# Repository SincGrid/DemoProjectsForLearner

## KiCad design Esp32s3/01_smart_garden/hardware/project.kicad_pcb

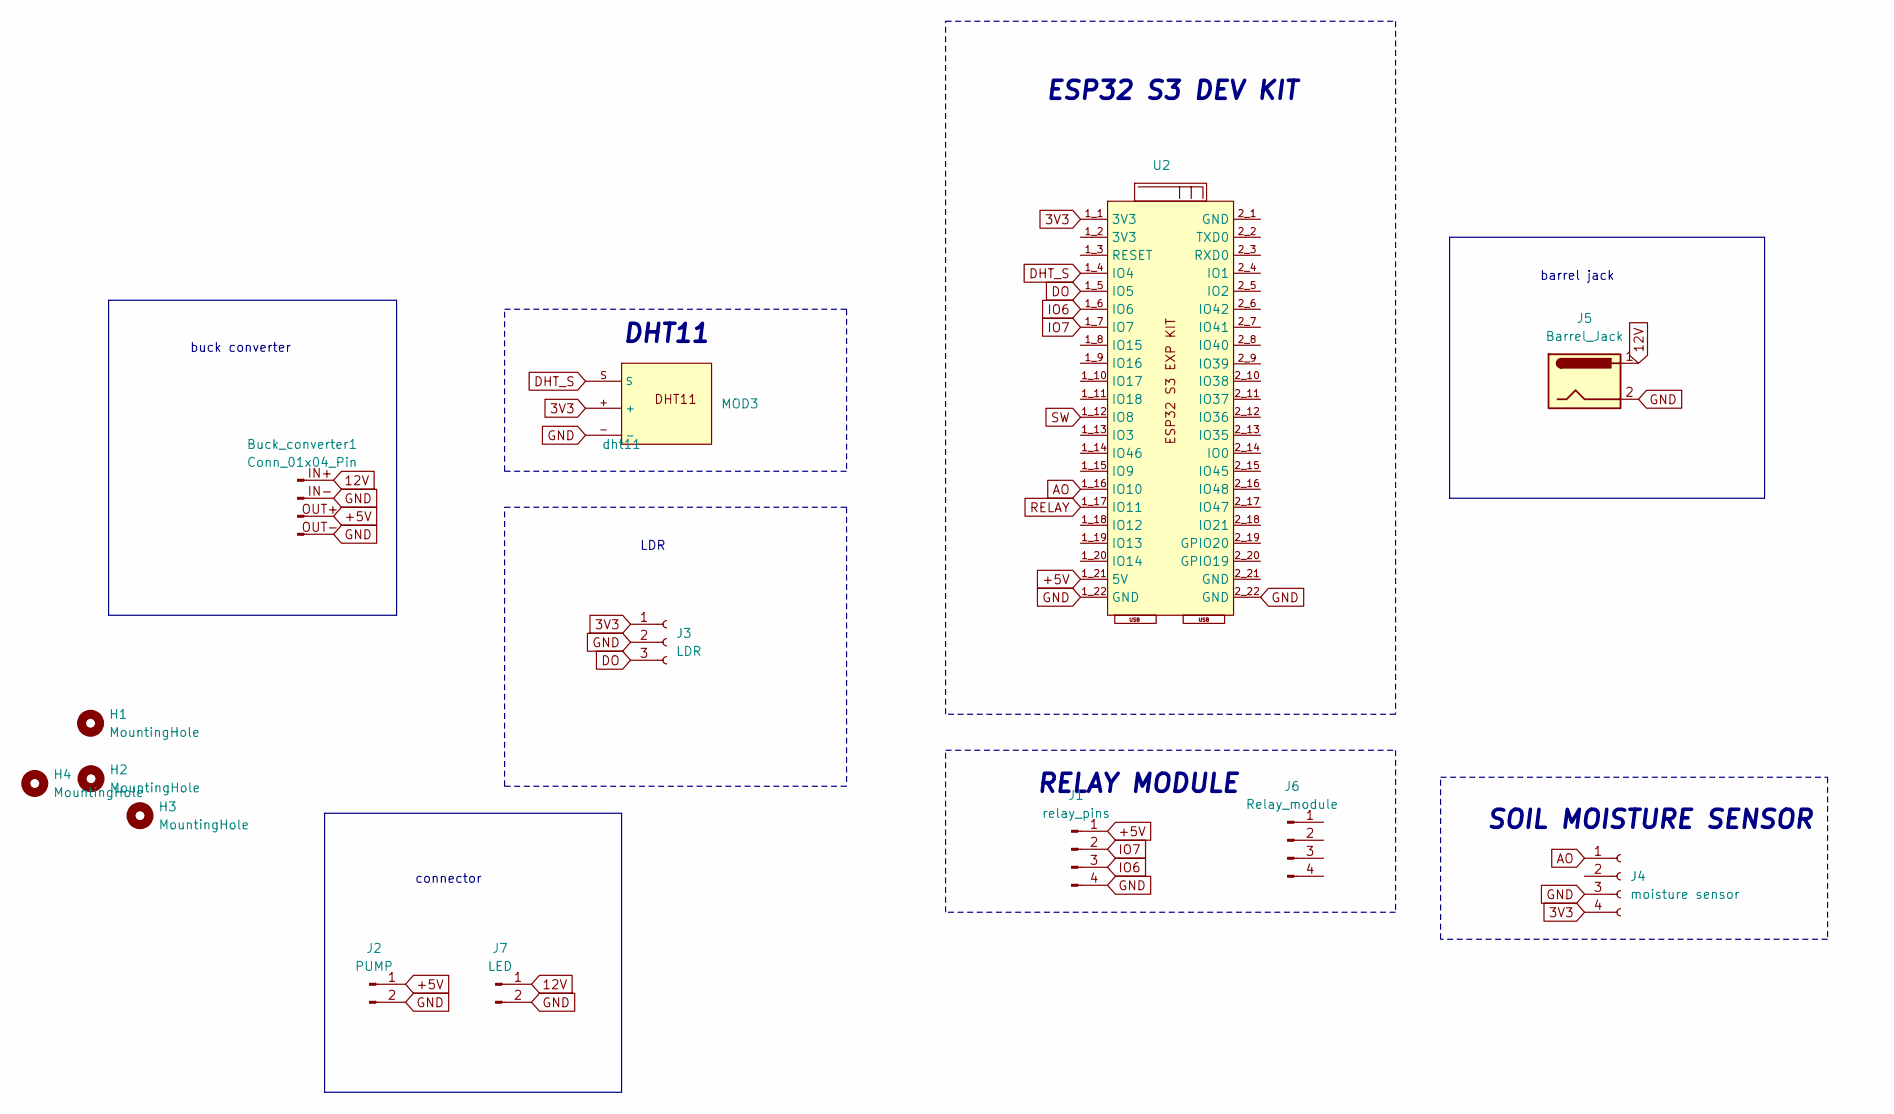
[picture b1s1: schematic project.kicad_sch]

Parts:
Buck_converter1: Conn_01x04_Pin; BUCK CONVERTER
H1, H2, H3, H4: MountingHole; MountingHole_2.5mm_Pad
J1: relay_pins; PinHeader_1x04_P2.54mm_Vertical
J2: PUMP; TE_282837-2
J3: LDR; JST_EH_B3B-EH-A_1x03_P2.50mm_Vertical
J4: moisture sensor; PinHeader_1x04_P2.54mm_Vertical
J5: Barrel_Jack; BarrelJack_Horizontal
J6: Relay_module; PinHeader_1x04_P2.54mm_Vertical
J7: LED; TE_282837-2
MOD3: dht11; PinHeader_1x03_P2.54mm_Vertical
U2: ESP32-S3BRD

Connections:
3V3: J3.1, J4.4, MOD3.+, U2.1_1 (3V3)
12V: Buck_converter1.IN+, J5.1, J7.1
+5V: Buck_converter1.OUT+, J1.1, J2.1, U2.1_21 (5V)
AO: J4.1, U2.1_16 (IO10)
DHT_S: MOD3.S, U2.1_4 (IO4)
DO: J3.3, U2.1_5 (IO5)
GND: Buck_converter1.IN-, Buck_converter1.OUT-, J1.4, J2.2, J3.2, J4.3, J5.2, J7.2, MOD3.-, U2.1_22 (GND), U2.2_22 (GND)
IO6: J1.3, U2.1_6 (IO6)
IO7: J1.2, U2.1_7 (IO7)
RELAY: U2.1_17 (IO11)
SW: U2.1_12 (IO8)

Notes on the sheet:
DHT11
LDR
ESP32 S3 DEV KIT
RELAY MODULE
connector
SOIL MOISTURE SENSOR
buck converter
barrel jack

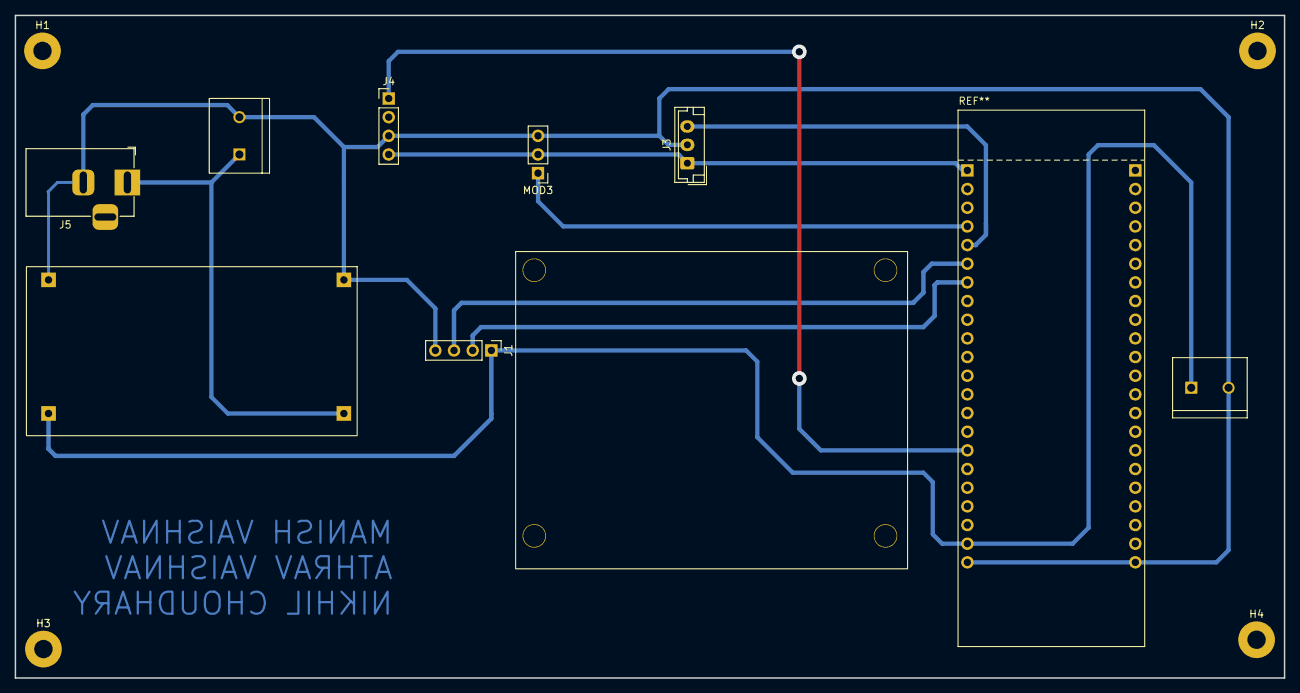
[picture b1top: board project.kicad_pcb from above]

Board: 2 copper layers, 172.7 x 90.2 mm, 14 parts (0 on the bottom side), 9 nets.

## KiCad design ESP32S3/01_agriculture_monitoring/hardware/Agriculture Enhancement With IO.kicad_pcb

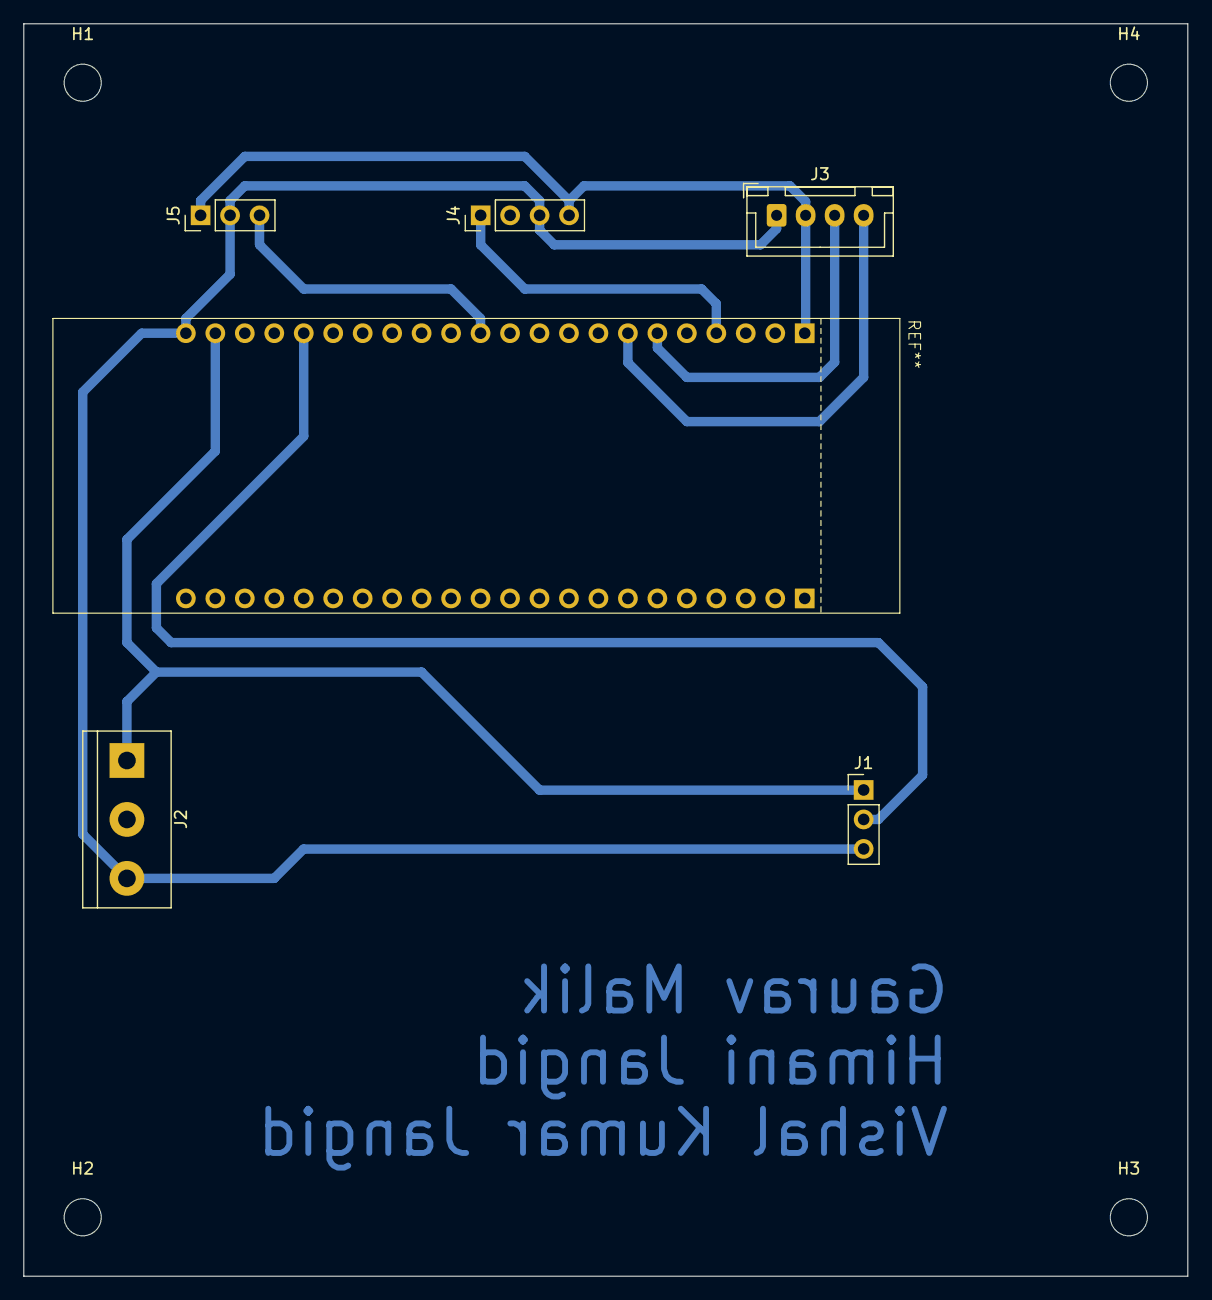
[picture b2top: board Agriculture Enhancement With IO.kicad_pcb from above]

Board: 2 copper layers, 100.3 x 108.0 mm, 10 parts (0 on the bottom side), 8 nets.

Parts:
H1, H2, H3, H4: MountingHole; MountingHole_3.2mm_M3
J1, J5: Conn_01x03_Socket; PinHeader_1x03_P2.54mm_Vertical
J2: Conn_01x03_Socket; TerminalBlock_bornier-3_P5.08mm
J3: Conn_01x04_Socket; JST_XH_B4B-XH-A_1x04_P2.50mm_Vertical
J4: Conn_01x04_Socket; PinHeader_1x04_P2.54mm_Vertical
U2: ESP32-S3BRD

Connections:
3V3: J3.2, J4.4, J5.1, U2.1_1 (3V3)
+5V: J1.1, J2.1, U2.1_21 (5V)
AO: J4.1, U2.1_4 (IO4)
DO_LDR: J5.3, U2.1_12 (IO8)
GND: J1.3, J2.3, J3.1, J4.3, J5.2, U2.1_22 (GND)
RELAY: J1.2, U2.1_18 (IO12)
SCL: J3.4, U2.1_7 (IO7)
SDA: J3.3, U2.1_6 (IO6)

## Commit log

2023-08-22 Create Readme.md
    readme Added
2023-08-22 agri addded
2023-08-22 added software files
2023-08-22 smart garden added
